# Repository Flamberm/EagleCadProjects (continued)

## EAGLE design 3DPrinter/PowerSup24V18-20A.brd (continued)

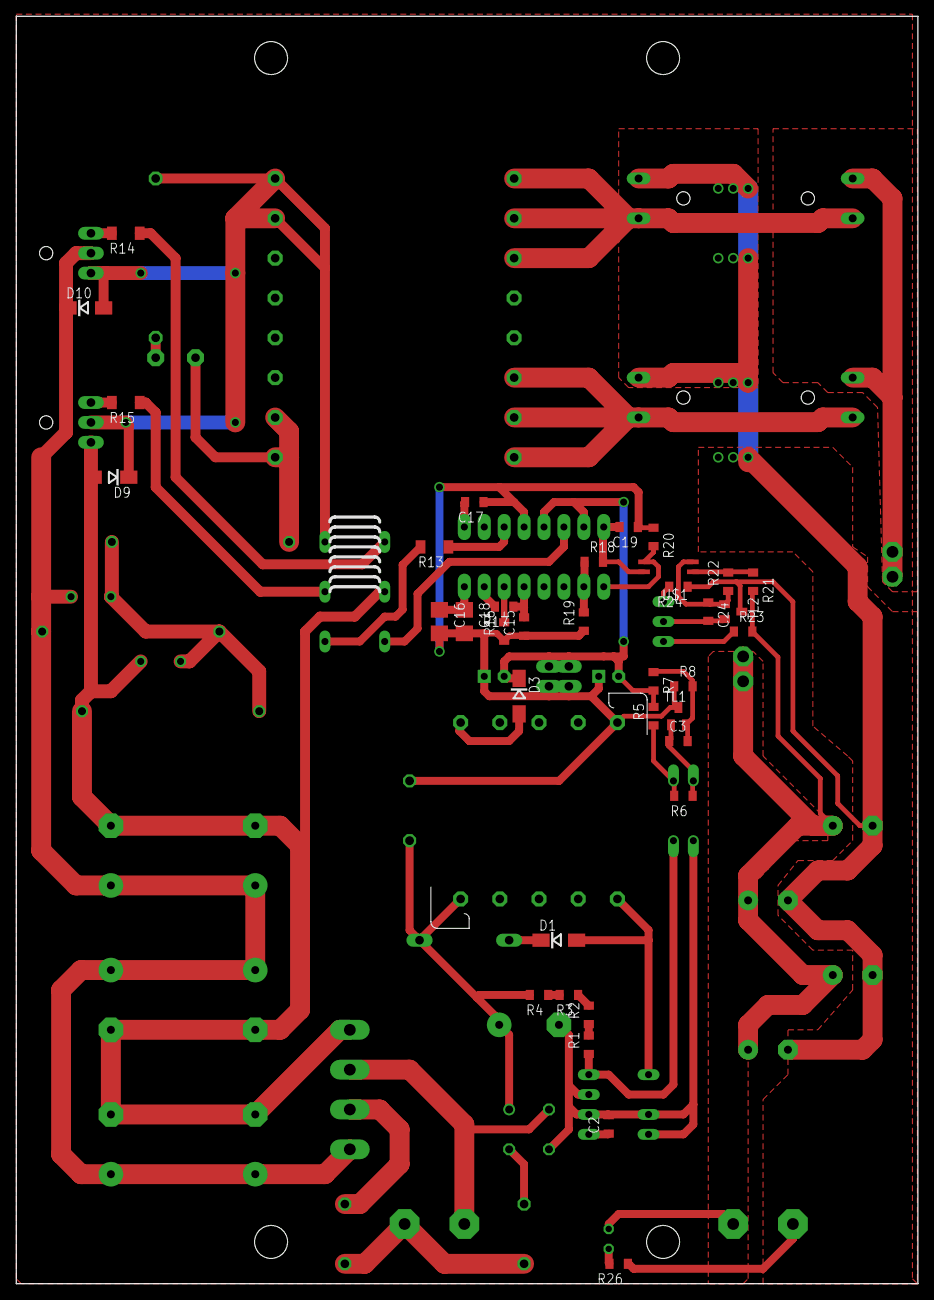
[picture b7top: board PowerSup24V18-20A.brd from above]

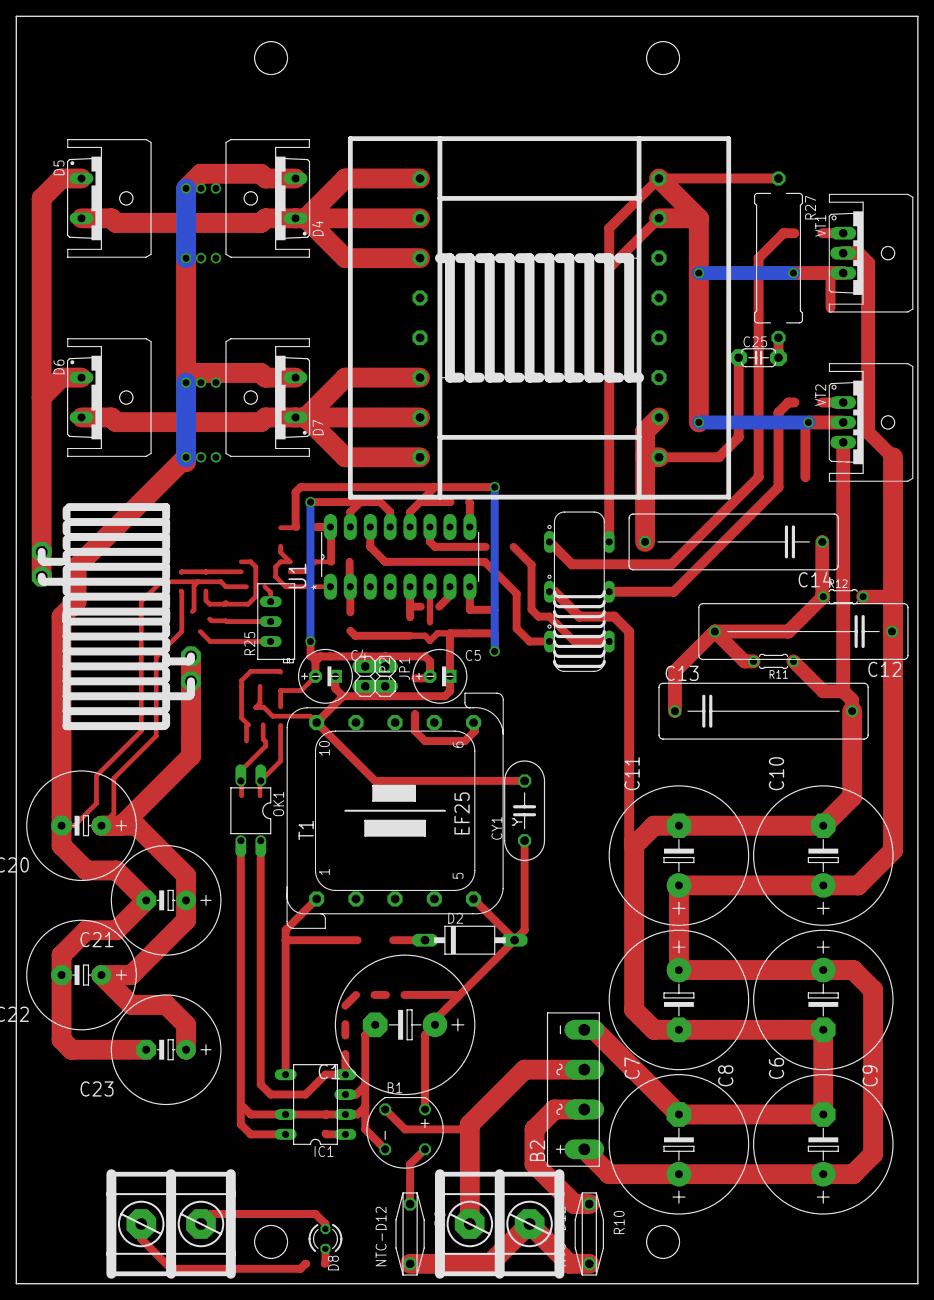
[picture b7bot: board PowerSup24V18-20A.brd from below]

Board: 2 copper layers, 115.0 x 161.7 mm, 87 parts (51 on the bottom side), 51 nets.

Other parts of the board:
U$2, U$3, U$4, U$5, U$6, U$7: SK95-3M3_HOLE

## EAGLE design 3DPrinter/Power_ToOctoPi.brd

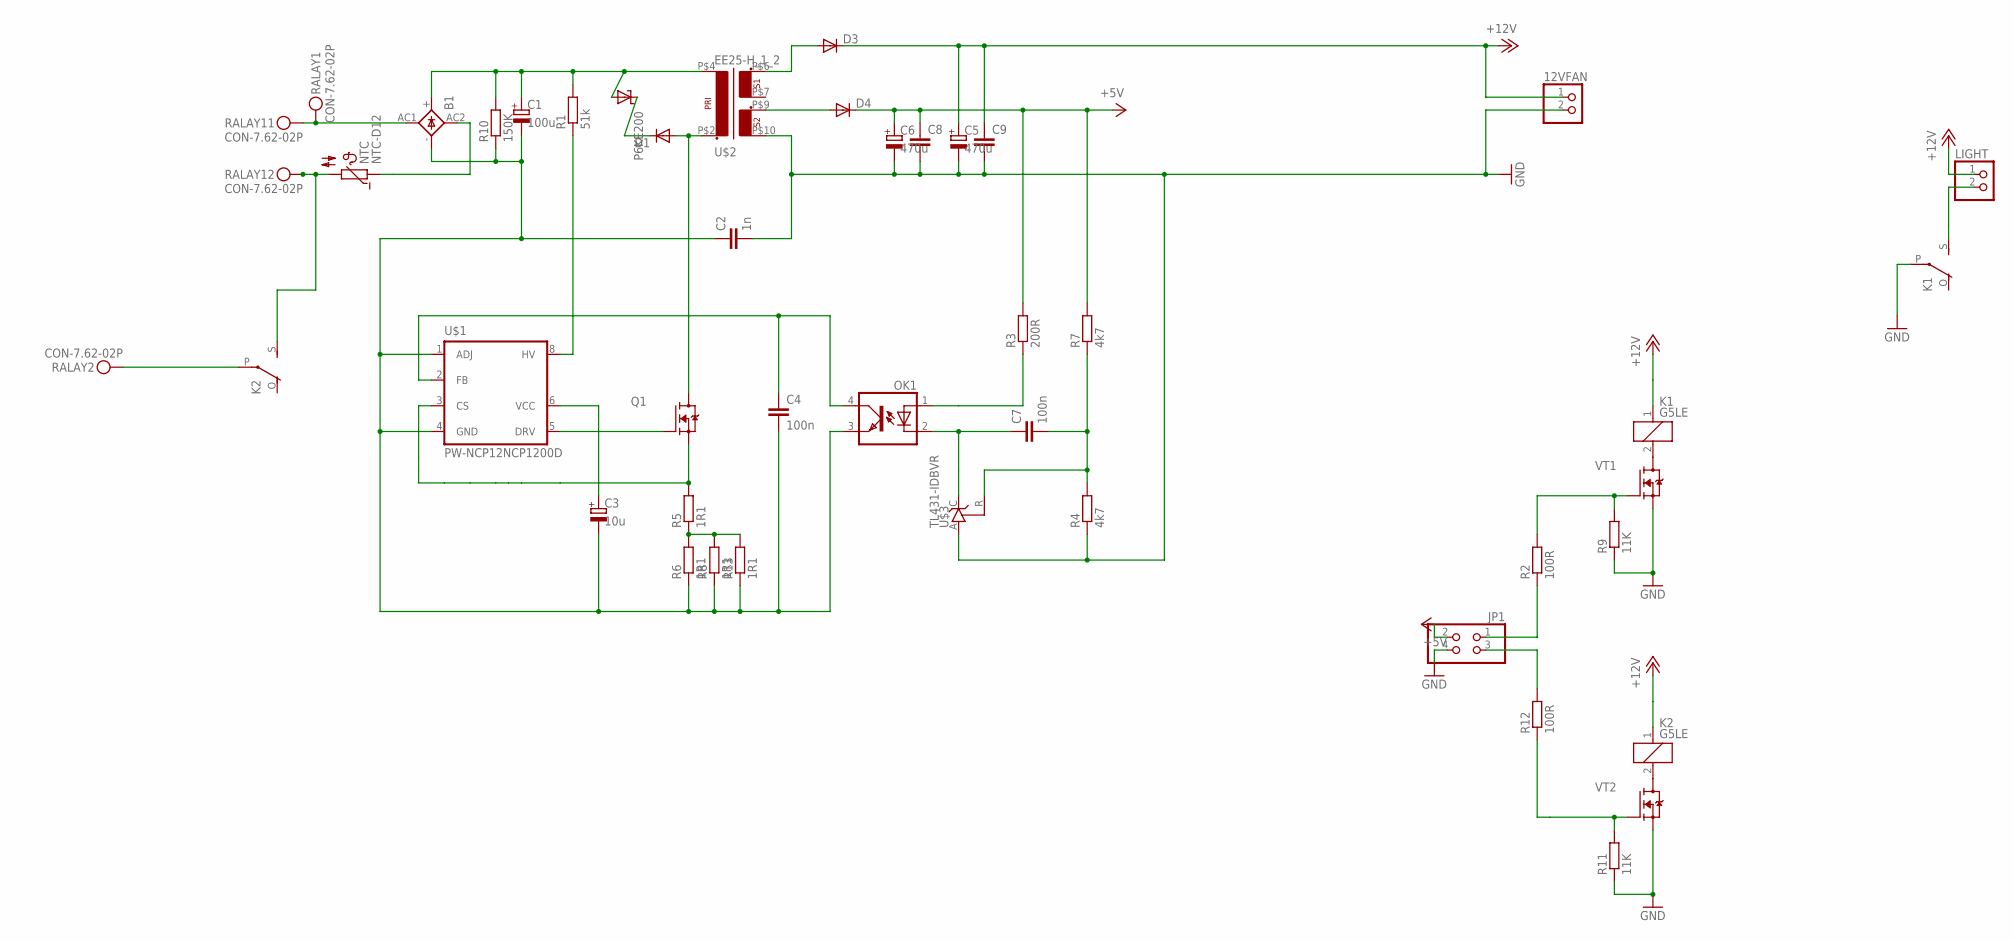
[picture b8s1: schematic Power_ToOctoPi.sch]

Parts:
12VFAN: PINHD-1X2; 1X02
B1: KBL
C1: 100u; C_D25-G10-CLAMP
C2: 1n; C050-024X044
C3: 10u; E2,5-7
C4, C7: 100n; C1206
C5, C6: 470u; E5-10,5
C8, C9: CAP_0805; C0805
D1, D3, D4: DIODE_ES1J; DO214AC
JP1: PINHD-2X2; 2X02
K1, K2: G5LE
LIGHT: PINHD-1X2; 1X02
NTC: NTC-D12
OK1: OPTOTRANSPC817; DIL04
P6KE200: SUPRESSORDO-204AC; DO15-12
Q1: FET-NTO-220; TO-220V
R1: 51k; SQP-5
R2, R12: 100R; R0805
R3: 200R; R1206
R4, R7: 4k7; R1206
R5, R6, R8, R13: 1R1; R1206
R9, R11: 11K; R0805
R10: 150K; MF-0125
RALAY, RALAY1: CON-7.62-02P; KF25C-7.62-02P-13
U$1: PW-NCP12NCP1200D; SO8
U$2: EE25-H_1_2; EE25
U$3: TL431-IDBVR; SOT23-5
VT1, VT2: FET-NPF-6X5; POWERFLAT-5X6

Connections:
+5V: C6.+, C8.1, D4.C, JP1.2, R3.2, R7.2
+12V: 12VFAN.1, C5.+, C9.1, D3.C, K1.1, K2.1, LIGHT.1
GND: 12VFAN.2, C2.2, C5.-, C6.-, C8.2, C9.2, JP1.4, K1.P, R4.1, R9.1, R11.1, U$2.P$10 (6), U$3.A, VT1.S1 (S), VT1.S2 (S), VT1.S3 (S), VT2.S1 (S), VT2.S2 (S), VT2.S3 (S)
unnamed: K2.S, NTC.2, RALAY1.P$2
unnamed: B1.AC1 (AC2), RALAY.P$1, RALAY1.P$1
unnamed: B1.AC2 (AC1), NTC.1
unnamed: R5.1, R6.2, R8.2, R13.2
unnamed: B1.-, C1.-, C2.1, C3.-, C4.2, OK1.3 (EMIT), R6.1, R8.1, R10.1, R13.1, U$1.1 (ADJ), U$1.4 (GND)
unnamed: B1.+, C1.+, P6KE200.A, R1.2, R10.2, U$2.P$4 (2)
unnamed: D1.C, P6KE200.C
unnamed: D1.A, Q1.2 (D), U$2.P$2 (1)
unnamed: K1.2, VT1.D1 (D)
unnamed: R1.1, U$1.8 (HV)
unnamed: Q1.1 (G), U$1.5 (DRV)
unnamed: Q1.3 (S), R5.2, U$1.3 (CS)
unnamed: JP1.1, R2.1
unnamed: C3.+, U$1.6 (VCC)
unnamed: C4.1, OK1.4 (COL), U$1.2 (FB)
unnamed: D3.A, U$2.P$6 (3)
unnamed: JP1.3, R12.2
unnamed: C7.2, R4.2, R7.1, U$3.R
unnamed: OK1.1 (A), R3.1
unnamed: D4.A, U$2.P$9 (5)
unnamed: C7.1, OK1.2 (C), U$3.C
unnamed: R2.2, R9.2, VT1.G
unnamed: R11.2, R12.1, VT2.G
unnamed: K1.S, LIGHT.2
unnamed: K2.2, VT2.D1 (D)
unnamed: K2.P, RALAY.P$2

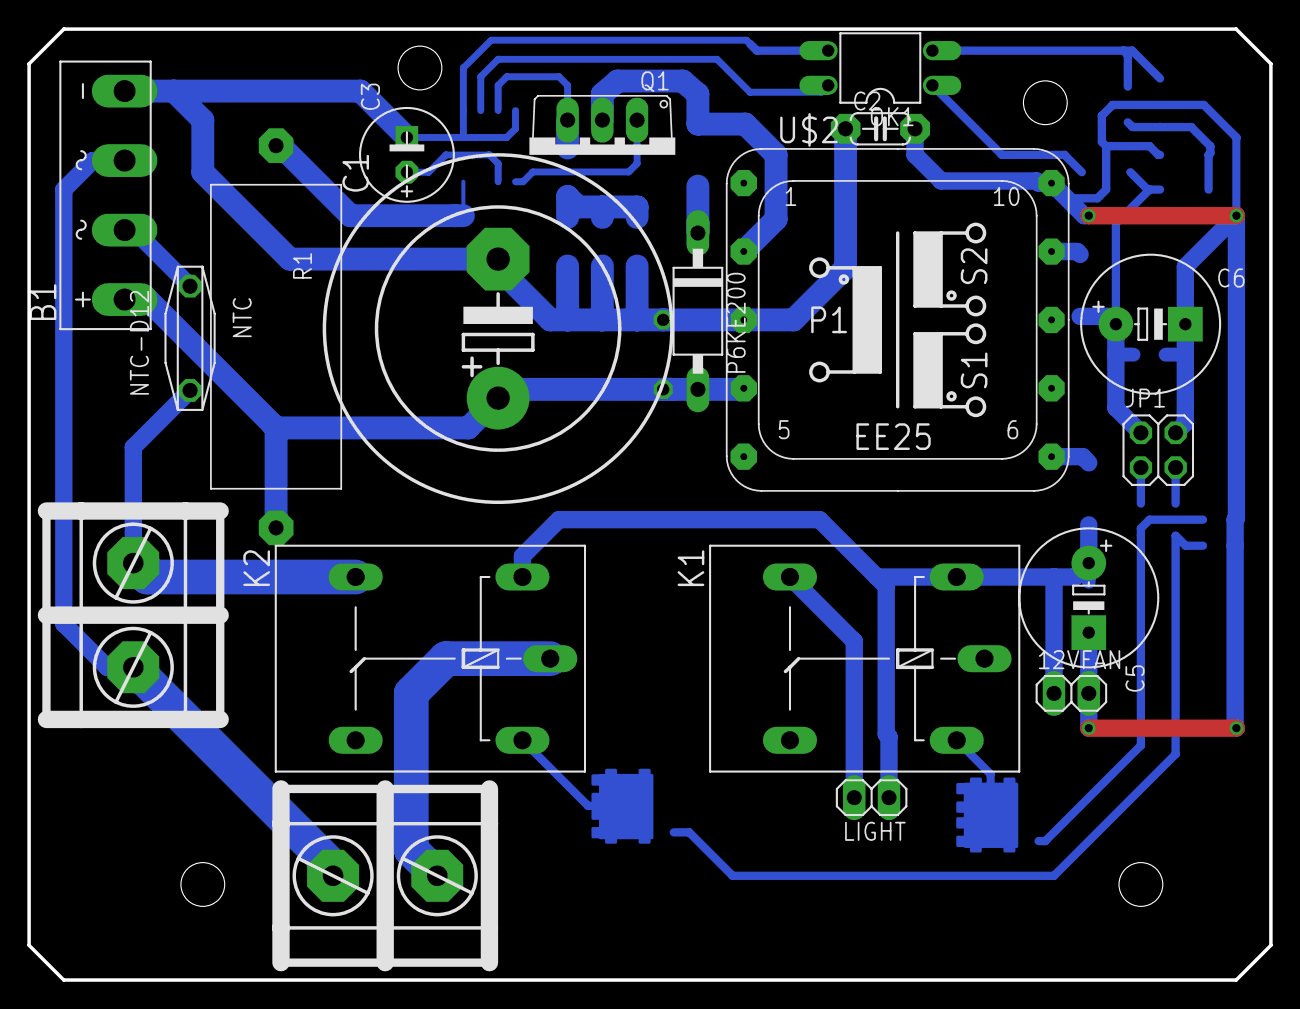
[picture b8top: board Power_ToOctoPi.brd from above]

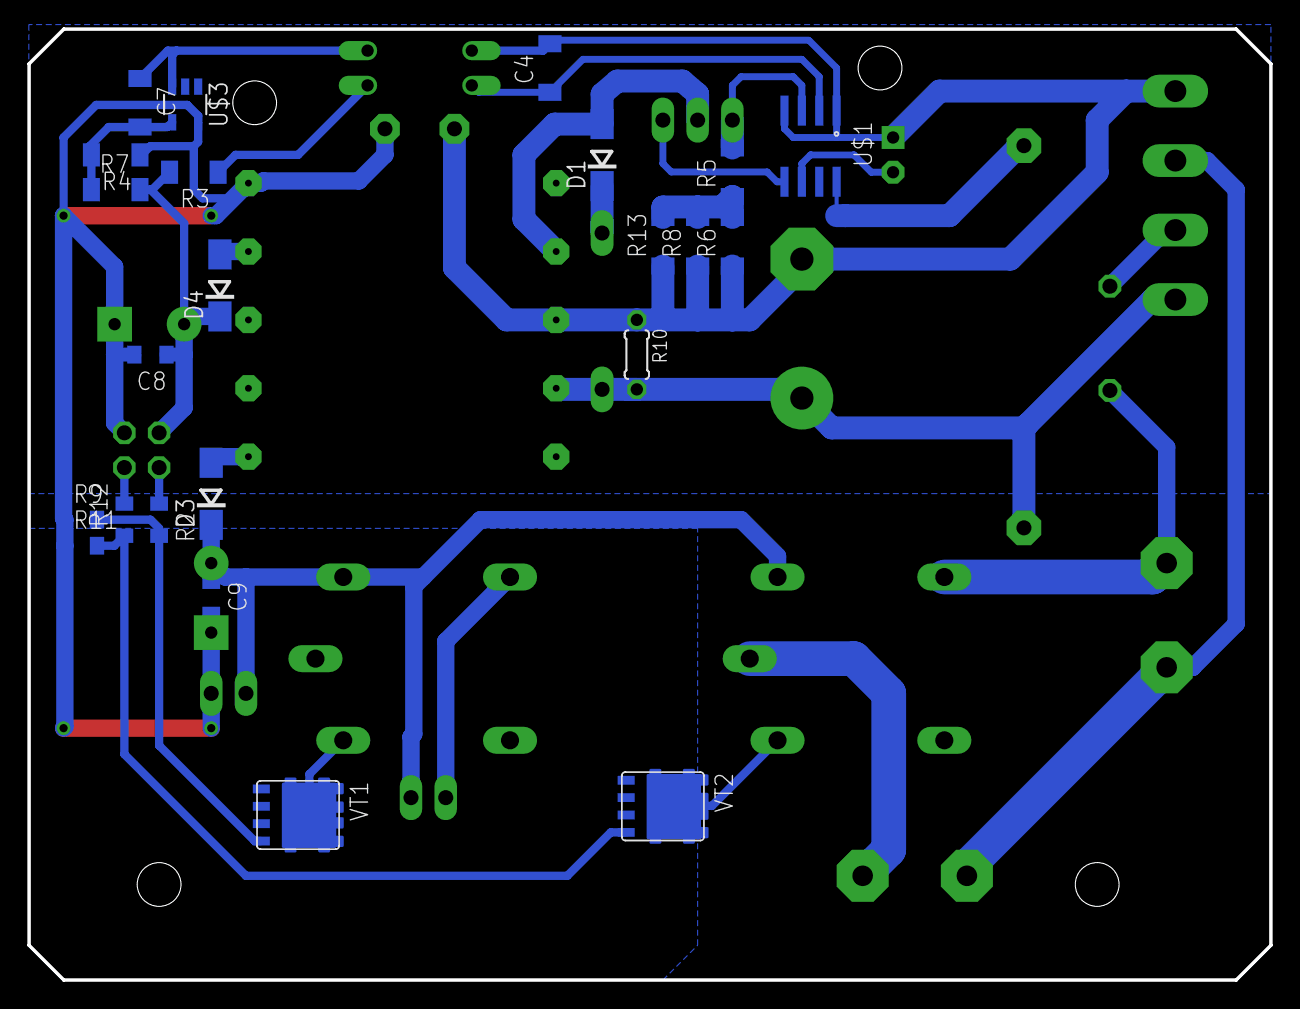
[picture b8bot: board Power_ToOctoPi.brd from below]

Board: 2 copper layers, 90.8 x 69.5 mm, 42 parts (23 on the bottom side), 29 nets.
